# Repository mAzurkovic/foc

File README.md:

# FOC controller for a 7025 drone motor

Field-oriented control of a 7025 hobby motor (420 kV, 28 poles) with current,
speed and position loops, running at 20 kHz on an STM32, with space-vector
modulation, planned position moves and a measured cogging-torque table.

## Hardware

| Part | Used here |
|---|---|
| Controller | NUCLEO-F446RE |
| Driver | BOOSTXL-DRV8305EVM (3-PWM mode, low-side shunts) |
| Encoder | AS5048A over SPI, powered from 3.3 V |
| Supply | 12 V 10 A mains adapter (cannot absorb braking energy) |

Wiring, Nucleo Arduino-header names:

| Signal | Pin |
|---|---|
| DRV8305 PWMHA / PWMHB / PWMHC | D7 / D8 / D2 |
| DRV8305 SCS, ENGATE, FAULT | D9, D6, D5 |
| DRV8305 ISENA / ISENB / ISENC, VSENPVDD | A0 / A1 / A2, A3 |
| AS5048A CSn | D10 |
| Shared SPI: SCK, MISO, MOSI | D13, D12, D11 |
| AS5048A 3.3V and 5V pins | both to Nucleo 3V3 |

Leave the DRV8305 board's own 3.3V pin unconnected.

## Layout

- `nucleo_foc/` — the controller. This is the sketch to use.
- `legacy/` — earlier steps, kept for reference: Arduino Uno bring-up and
  control sketches (`drv8305_*`, `encoder_read`, ...), tests for a
  DRV8323RS board that turned out to have a faulty phase, and the Nucleo
  bring-up sketches. `legacy/nucleo_check` (wiring check, no PWM) and
  `legacy/nucleo_pwm_test` (resistance and inductance measurement) are still
  useful when changing hardware.
- `docs/` — driver and evaluation-board datasheets.

## Running it

Arduino IDE with the "STM32 MCU based boards" package and STM32CubeProgrammer.
Tools: Board **Nucleo-64**, Board part number **Nucleo F446RE**, Upload method
**STM32CubeProgrammer (SWD)**. Serial Monitor at 115200 baud, line ending
**Newline**.

Clamp the motor, nothing on the shaft, then type `g`.

| Command | Effect |
|---|---|
| `p<deg>` | planned move to an angle (accelerate, cruise, brake), then hold; prints the time taken |
| `v<rpm>` | speed control (up to 1000) |
| `q<amps>`, `d<amps>` | torque current, and d-axis current (no torque) |
| `s` | hold the present position |
| `x` | outputs off, motor coasts |
| `a` | re-measure encoder offset and direction |
| `C` | scan cogging torque and store the table in flash |
| `t` | measure acceleration per amp and retune the outer loops |
| `c0` / `c1` | cogging and friction feed-forward off / on |
| `W`, `R`, `B`, `O`, `D`, `P`, `K`, `I` | loop bandwidths, spacing and gains |
| `m<rows>` | status rows per second, `m0` for none |

Settings typed at run time are lost on reset; the defaults live at the top of
the sketch. The cogging table is the exception: it is kept in flash.

## Measured values (the sketch's defaults)

| Quantity | Value |
|---|---|
| Phase resistance, inductance | 0.030 Ω, 5.5 µH |
| Pole pairs | 14 |
| Back-EMF | about 1.75 mV per rpm (phase amplitude) |
| Acceleration per amp, bare shaft | 2900 rpm/s per A |
| Loop bandwidths | current 500 Hz, speed 50 Hz, position 5 Hz |
| Limits | 12 A target, 18 A trip, 1000 rpm, 3 V phase voltage |
| Planned moves | up to 900 rpm, accelerate 20,000 rpm/s, brake 8,000 rpm/s |

## When something changes

- **Motor wires moved, or encoder magnet remounted:** run `a`, update
  `encoderOffset` and `direction` in the sketch, then run `C`.
- **Anything attached to the shaft:** run `t`; the stored tuning is for a bare
  rotor.
- **Different supply:** braking energy is burned in the motor windings because
  this adapter shuts down when current flows back into it. The thresholds
  (`BUS_DUMP_START_VOLTS` and neighbours) assume a 12 V bus.

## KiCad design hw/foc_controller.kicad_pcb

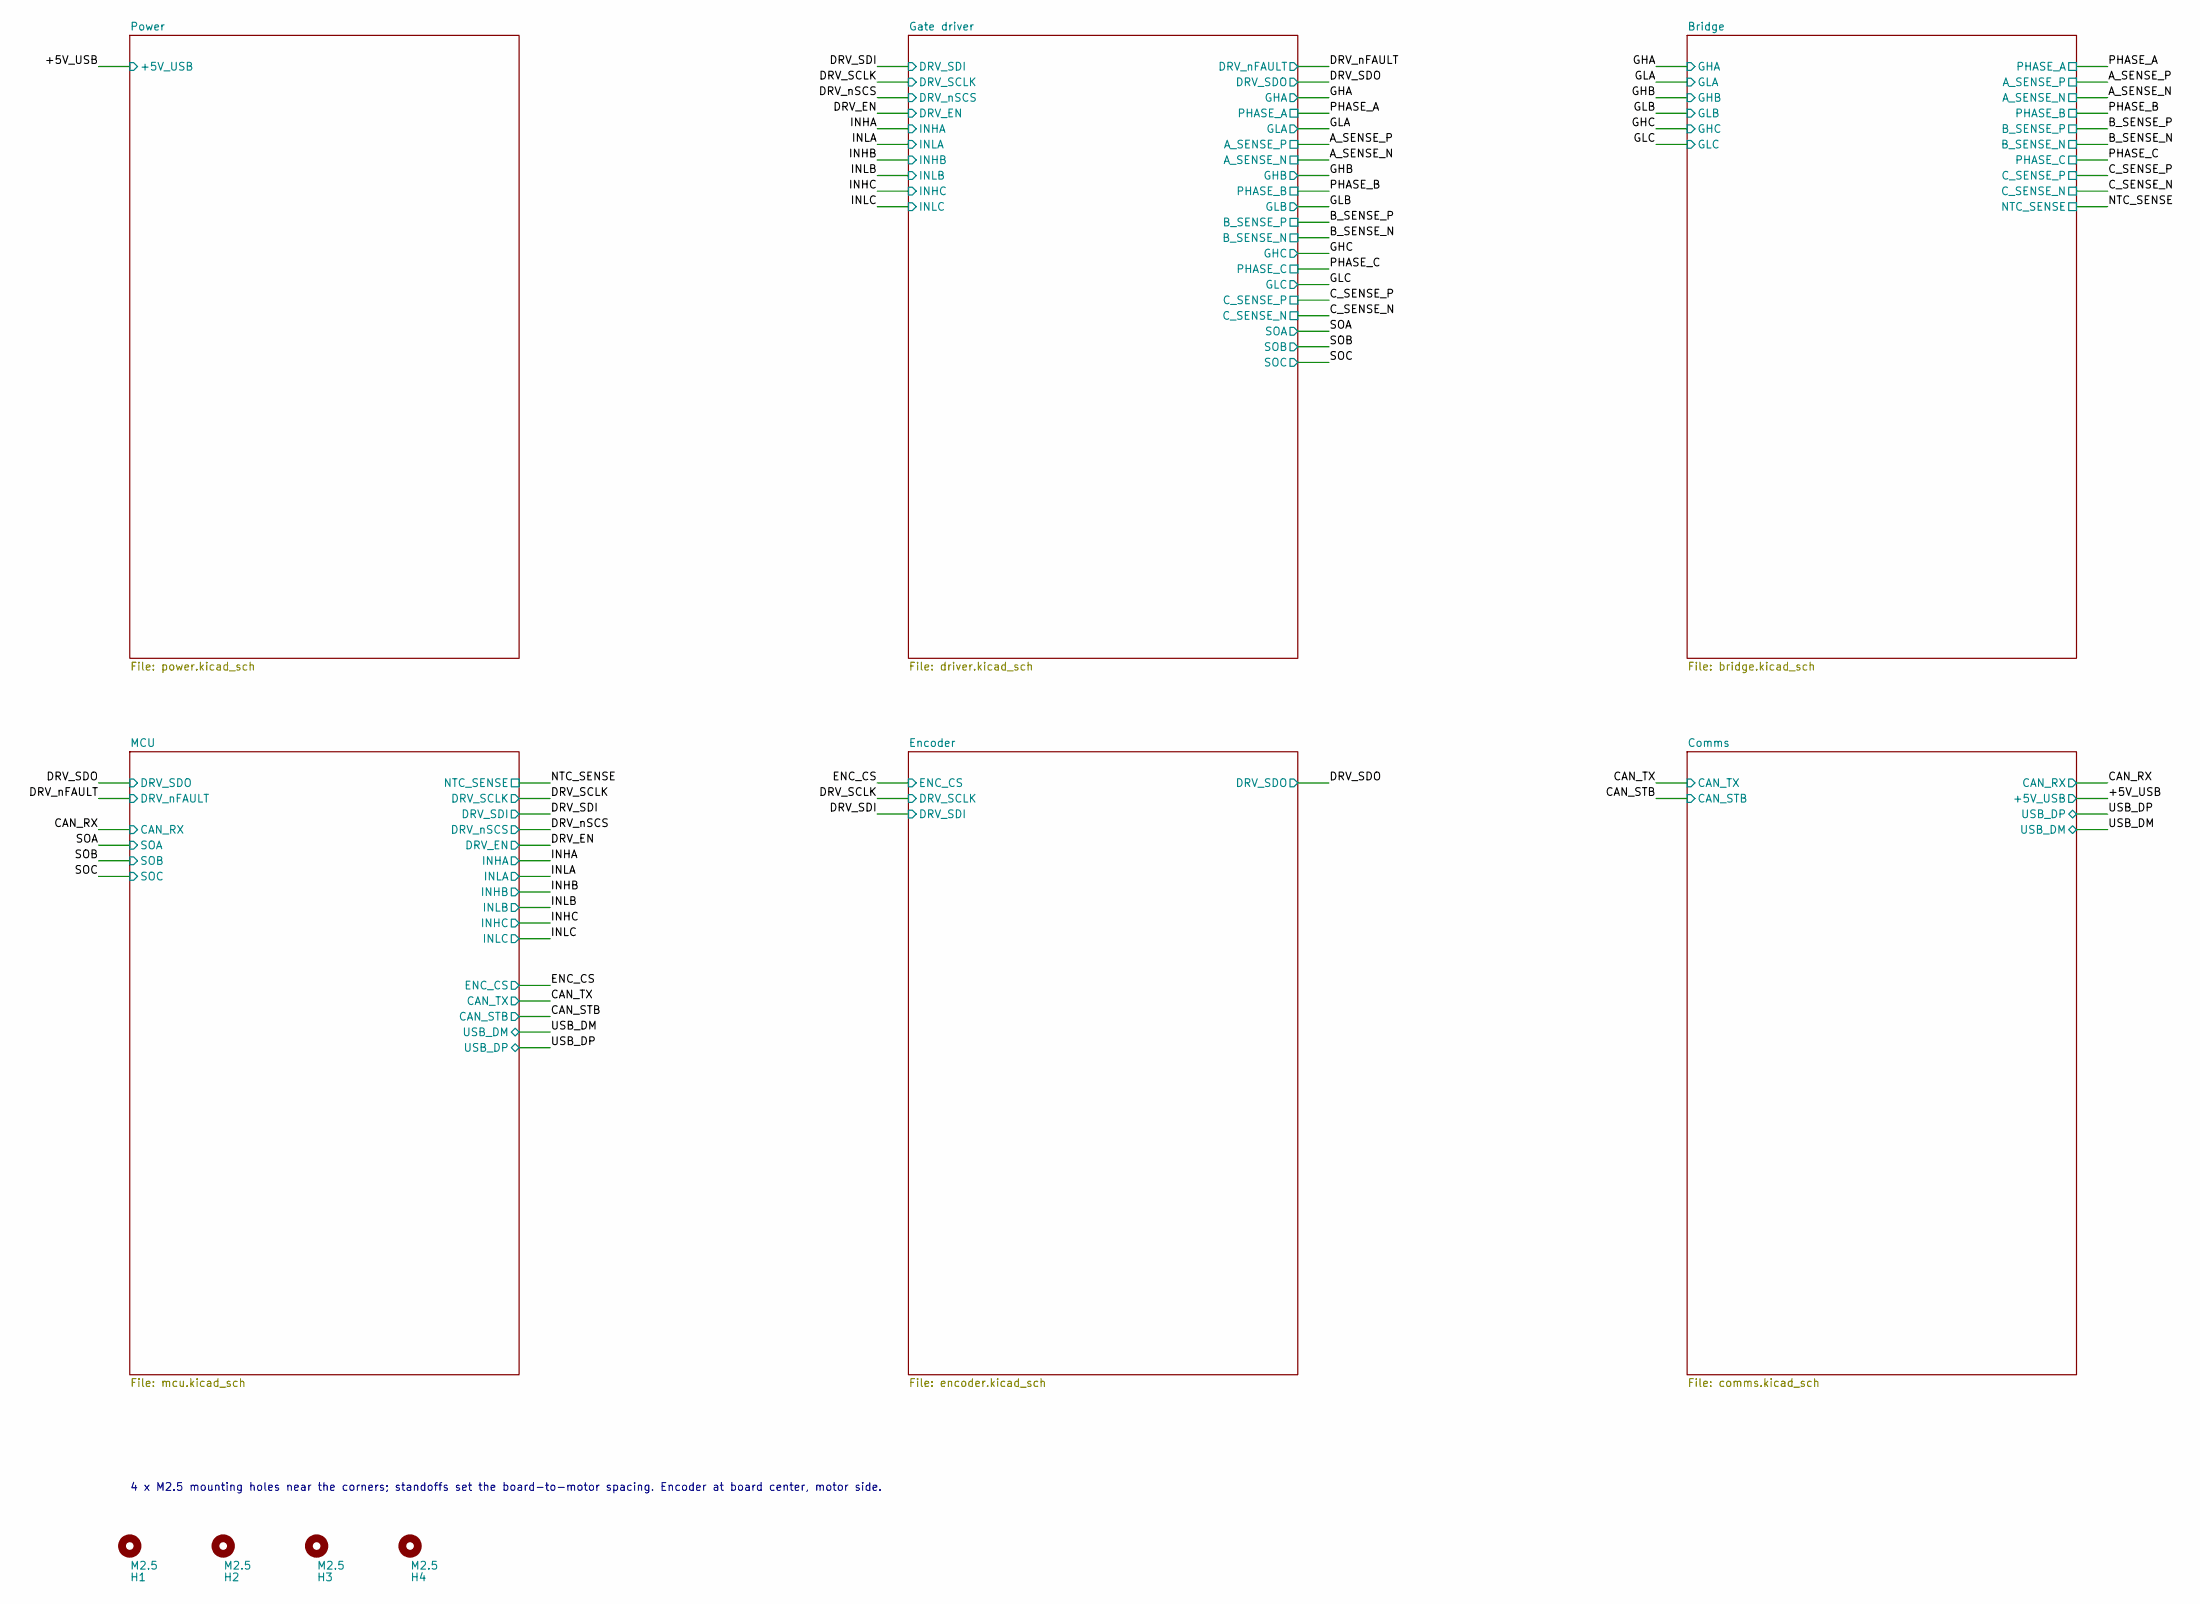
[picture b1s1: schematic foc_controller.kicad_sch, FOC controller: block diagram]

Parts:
H1, H2, H3, H4: M2.5; MountingHole_2.7mm_M2.5

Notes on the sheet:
4 x M2.5 mounting holes near the corners; standoffs set the board-to-motor spacing. Encoder at board center, motor side.

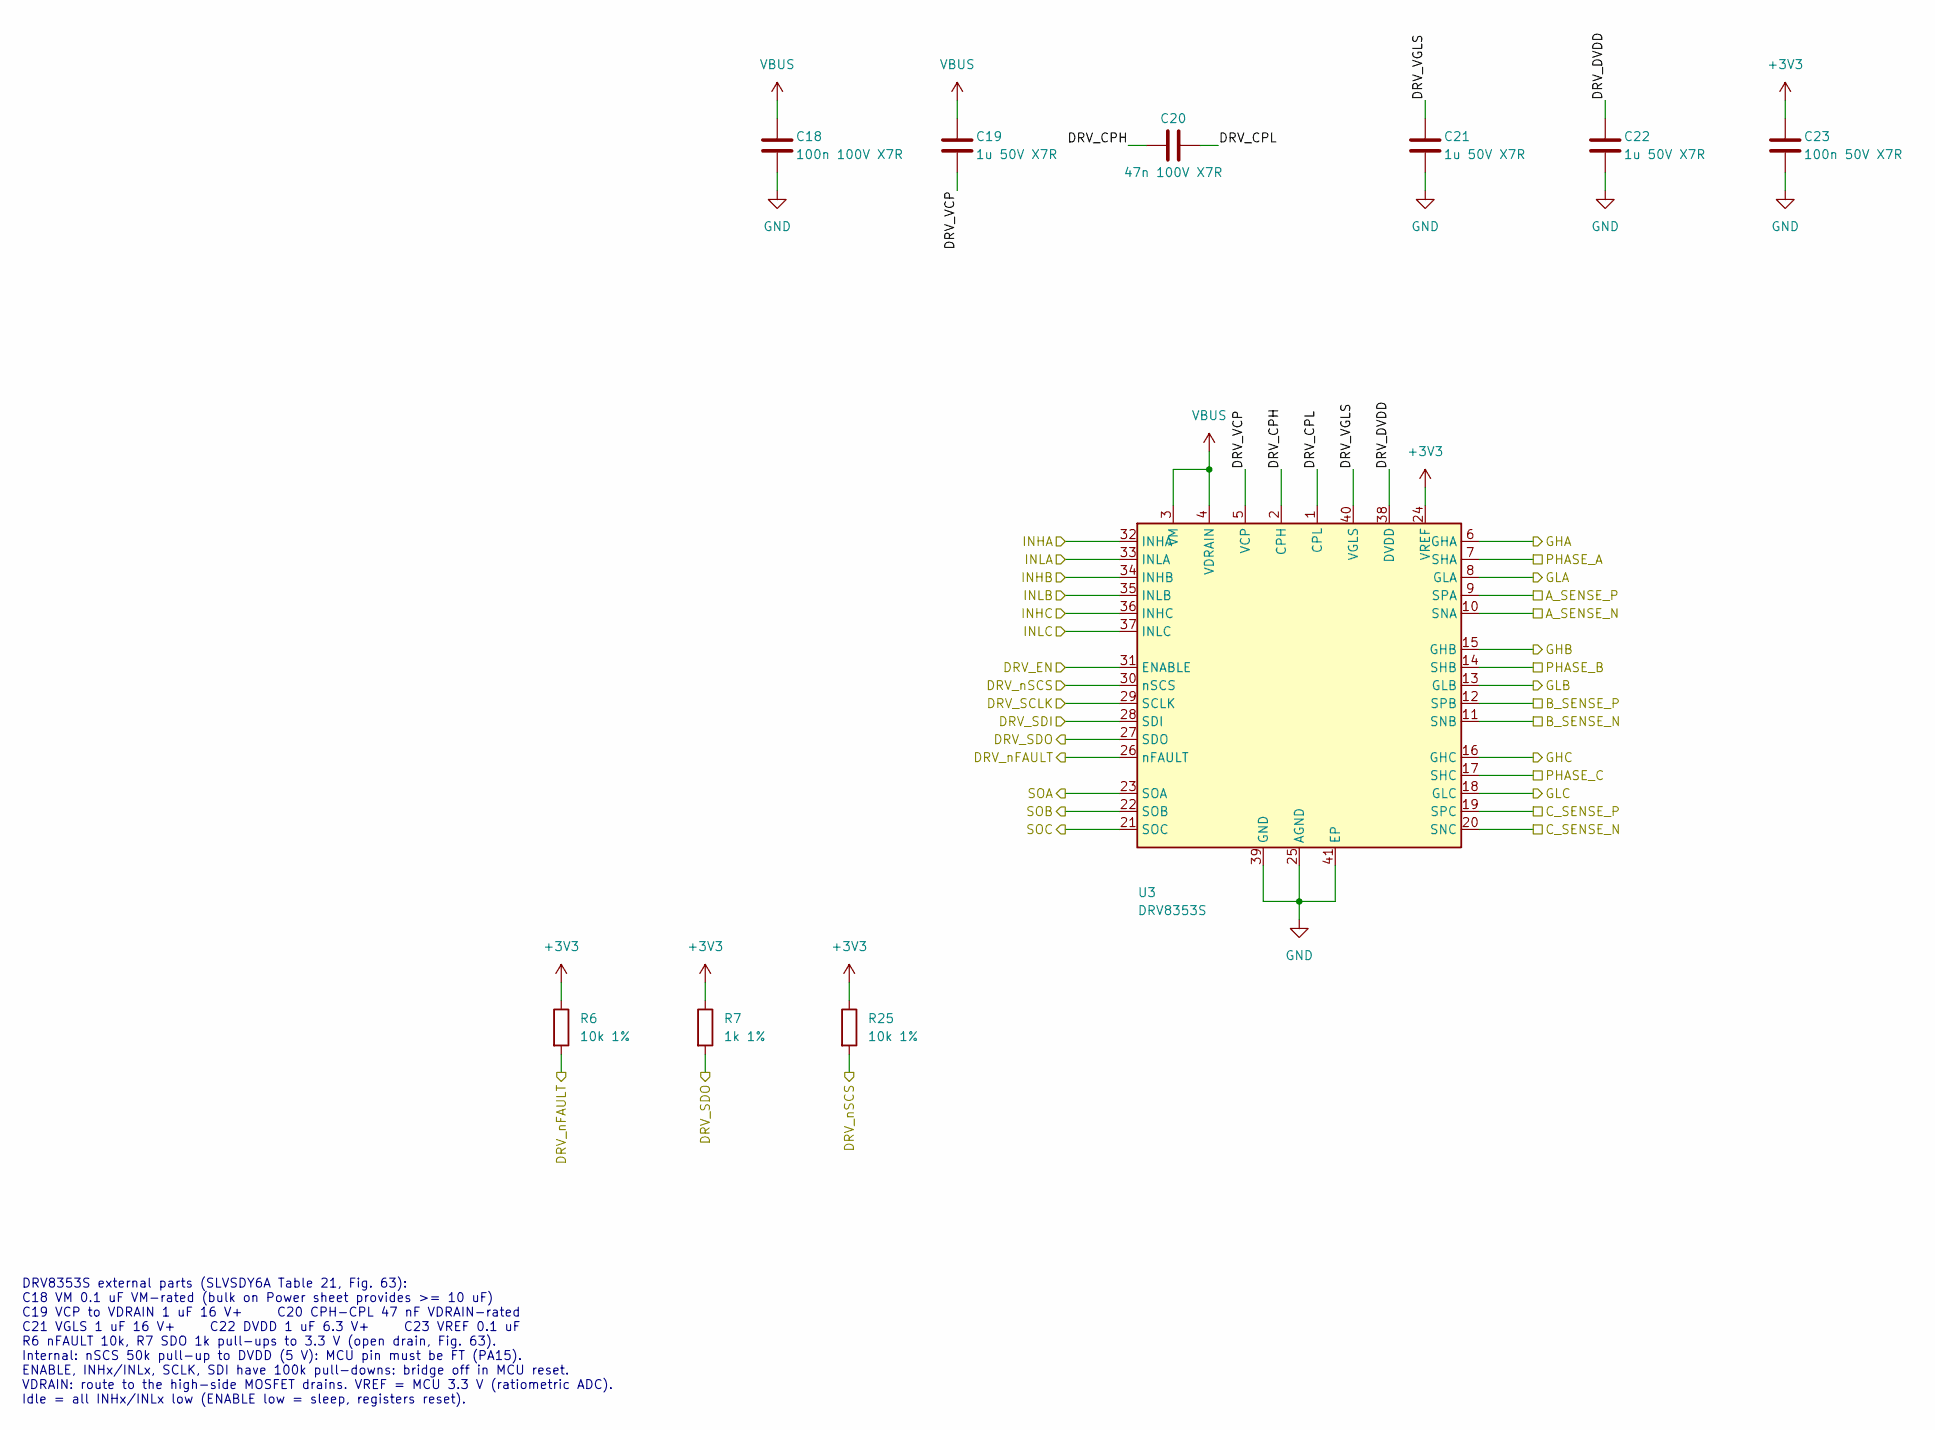
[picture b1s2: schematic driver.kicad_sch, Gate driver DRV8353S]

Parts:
C18: 100n 100V X7R; C_0603_1608Metric; MPN CC0603KRX7R0BB104; LCSC C113803
C19, C21, C22: 1u 50V X7R; C_0805_2012Metric; MPN CL21B105KBFNNNE; LCSC C28323
C20: 47n 100V X7R; C_0805_2012Metric; MPN CL21B473KCFNNNE; LCSC C17074
C23: 100n 50V X7R; C_0402_1005Metric; MPN CL05B104KB54PNC; LCSC C307331
R6, R25: 10k 1%; R_0402_1005Metric; MPN 0402WGF1002TCE; LCSC C25744
R7: 1k 1%; R_0402_1005Metric; MPN 0402WGF1001TCE; LCSC C11702
U3: DRV8353S; WQFN-40_L6.0-W6.0-P0.50-TL-EP4.2; MPN DRV8353SRTAT; LCSC C2150480

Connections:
+3V3: C23.1, R6.1, R7.1, R25.1, U3.24 (VREF); also elsewhere on the board
/A_SENSE_N: U3.10 (SNA); also elsewhere on the board
/A_SENSE_P: U3.9 (SPA); also elsewhere on the board
/B_SENSE_N: U3.11 (SNB); also elsewhere on the board
/B_SENSE_P: U3.12 (SPB); also elsewhere on the board
/C_SENSE_N: U3.20 (SNC); also elsewhere on the board
/C_SENSE_P: U3.19 (SPC); also elsewhere on the board
/DRV_EN: U3.31 (ENABLE); also elsewhere on the board
/DRV_SCLK: U3.29 (SCLK); also elsewhere on the board
/DRV_SDI: U3.28 (SDI); also elsewhere on the board
/DRV_SDO: R7.2, U3.27 (SDO); also elsewhere on the board
/DRV_nFAULT: R6.2, U3.26 (nFAULT); also elsewhere on the board
/DRV_nSCS: R25.2, U3.30 (nSCS); also elsewhere on the board
/GHA: U3.6 (GHA); also elsewhere on the board
/GHB: U3.15 (GHB); also elsewhere on the board
/GHC: U3.16 (GHC); also elsewhere on the board
/GLA: U3.8 (GLA); also elsewhere on the board
/GLB: U3.13 (GLB); also elsewhere on the board
/GLC: U3.18 (GLC); also elsewhere on the board
/Gate driver/DRV_CPH: C20.1, U3.2 (CPH)
/Gate driver/DRV_CPL: C20.2, U3.1 (CPL)
/Gate driver/DRV_DVDD: C22.1, U3.38 (DVDD)
/Gate driver/DRV_VCP: C19.1, U3.5 (VCP)
/Gate driver/DRV_VGLS: C21.1, U3.40 (VGLS)
/INHA: U3.32 (INHA); also elsewhere on the board
/INHB: U3.34 (INHB); also elsewhere on the board
/INHC: U3.36 (INHC); also elsewhere on the board
/INLA: U3.33 (INLA); also elsewhere on the board
/INLB: U3.35 (INLB); also elsewhere on the board
/INLC: U3.37 (INLC); also elsewhere on the board
/PHASE_A: U3.7 (SHA); also elsewhere on the board
/PHASE_B: U3.14 (SHB); also elsewhere on the board
/PHASE_C: U3.17 (SHC); also elsewhere on the board
/SOA: U3.23 (SOA); also elsewhere on the board
/SOB: U3.22 (SOB); also elsewhere on the board
/SOC: U3.21 (SOC); also elsewhere on the board
GND: C18.2, C21.2, C22.2, C23.2, U3.25 (AGND), U3.39 (GND), U3.41 (EP); also elsewhere on the board
VBUS: C18.1, C19.2, U3.3 (VM), U3.4 (VDRAIN); also elsewhere on the board

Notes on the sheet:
DRV8353S external parts (SLVSDY6A Table 21, Fig. 63): C18 VM 0.1 uF VM-rated (bulk on Power sheet provides >= 10 uF) C19 VCP to VDRAIN 1 uF 16 V+ C20 CPH-CPL 47 nF VDRAIN-rated C21 VGLS 1 uF 16 V+ C22 DVDD 1 uF 6.3 V+ C23 VREF 0.1 uF R6 nFAULT 10k, R7 SDO 1k pull-ups to 3.3 V (open drain, Fig. 63).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

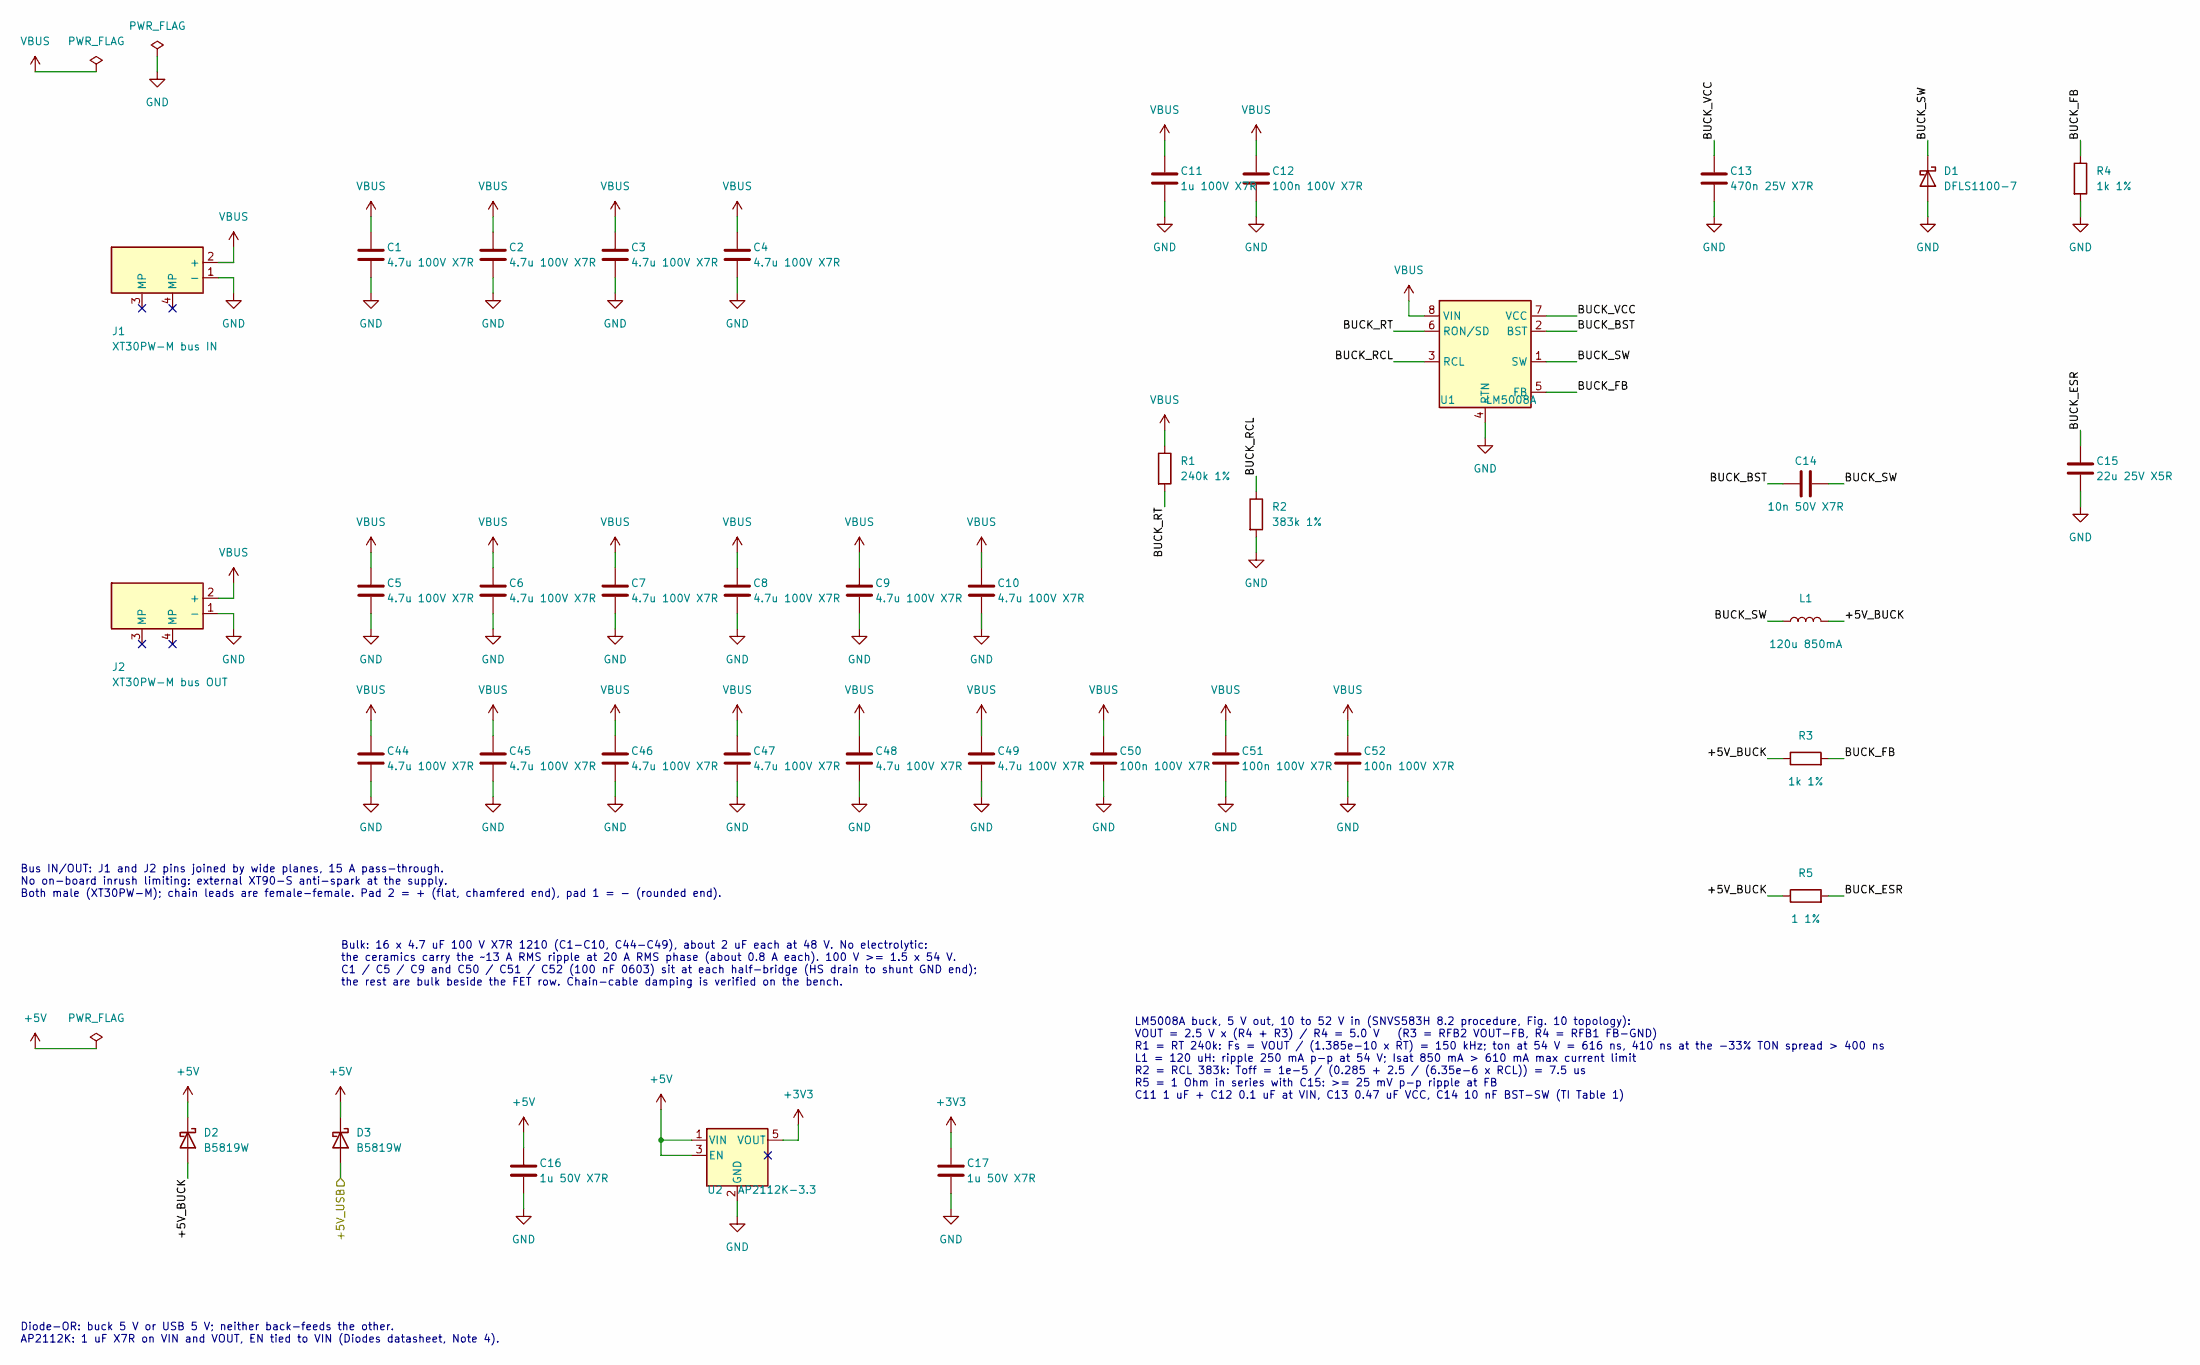
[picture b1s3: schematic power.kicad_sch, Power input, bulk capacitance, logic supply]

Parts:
C1, C2, C3, C4, C5, C6, C7, C8, C9, C10, C44, C45, C46, C47, C48, C49: 4.7u 100V X7R; C_1210_3225Metric; MPN FS32X475K101EGG; LCSC C381466
C11: 1u 100V X7R; C_1206_3216Metric; MPN CC1206KKX7R0BB105; LCSC C70463
C12, C50, C51, C52: 100n 100V X7R; C_0603_1608Metric; MPN CC0603KRX7R0BB104; LCSC C113803
C13: 470n 25V X7R; C_0603_1608Metric; MPN CL10B474KA8NNNC; LCSC C1623
C14: 10n 50V X7R; C_0603_1608Metric; MPN 0603B103K500NT; LCSC C57112
C15: 22u 25V X5R; C_1206_3216Metric; MPN CL31A226KAHNNNE; LCSC C12891
C16, C17: 1u 50V X7R; C_0805_2012Metric; MPN CL21B105KBFNNNE; LCSC C28323
D1: DFLS1100-7; D_PowerDI-123; MPN DFLS1100-7; LCSC C107674
D2, D3: B5819W; D_SOD-123; MPN B5819W SL; LCSC C8598
J1: XT30PW-M bus IN; CONN-TH_XT30PW-M-1; MPN XT30PW-M30.G.Y; LCSC C431092
J2: XT30PW-M bus OUT; CONN-TH_XT30PW-M-1; MPN XT30PW-M30.G.Y; LCSC C431092
L1: 120u 850mA; IND-SMD_L6.0-W6.0; MPN SWPA6045S121MT; LCSC C96952
R1: 240k 1%; R_0603_1608Metric; MPN RC0603FR-07240KL; LCSC C137765
R2: 383k 1%; R_0603_1608Metric; MPN 0603WAF3833T5E; LCSC C25816
R3, R4: 1k 1%; R_0402_1005Metric; MPN 0402WGF1001TCE; LCSC C11702
R5: 1 1%; R_0603_1608Metric; MPN 0603WAF100KT5E; LCSC C22936
U1: LM5008A; MSOP-8_3x3mm_P0.65mm; MPN LM5008AMMX/NOPB; LCSC C2071250
U2: AP2112K-3.3; SOT-23-5; MPN AP2112K-3.3TRG1; LCSC C51118

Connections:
+3V3: C17.1, U2.5 (VOUT); also elsewhere on the board
+5V: C16.1, D2.1 (K), D3.1 (K), U2.1 (VIN), U2.3 (EN)
/+5V_USB: D3.2 (A); also elsewhere on the board
/Power/+5V_BUCK: D2.2 (A), L1.2, R3.1, R5.1
/Power/BUCK_BST: C14.1, U1.2 (BST)
/Power/BUCK_ESR: C15.1, R5.2
/Power/BUCK_FB: R3.2, R4.1, U1.5 (FB)
/Power/BUCK_RCL: R2.1, U1.3 (RCL)
/Power/BUCK_RT: R1.2, U1.6 (RON/SD)
/Power/BUCK_SW: C14.2, D1.1 (K), L1.1, U1.1 (SW)
/Power/BUCK_VCC: C13.1, U1.7 (VCC)
GND: C1.2, C2.2, C3.2, C4.2, C5.2, C6.2, C7.2, C8.2, C9.2, C10.2, C11.2, C12.2, C13.2, C15.2, C16.2, C17.2, C44.2, C45.2, C46.2, C47.2, C48.2, C49.2, C50.2, C51.2, C52.2, D1.2 (A), J1.1 (-), J2.1 (-), R2.2, R4.2, U1.4 (RTN), U2.2 (GND); also elsewhere on the board
VBUS: C1.1, C2.1, C3.1, C4.1, C5.1, C6.1, C7.1, C8.1, C9.1, C10.1, C11.1, C12.1, C44.1, C45.1, C46.1, C47.1, C48.1, C49.1, C50.1, C51.1, C52.1, J1.2 (+), J2.2 (+), R1.1, U1.8 (VIN); also elsewhere on the board

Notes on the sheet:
Diode-OR: buck 5 V or USB 5 V; neither back-feeds the other. AP2112K: 1 uF X7R on VIN and VOUT, EN tied to VIN (Diodes datasheet, Note 4).
Bus IN/OUT: J1 and J2 pins joined by wide planes, 15 A pass-through. No on-board inrush limiting: external XT90-S anti-spark at the supply. Both male (XT30PW-M); chain leads are female-female. Pad 2 = + (flat, chamfered end), pad 1 = - (rounded end).
LM5008A buck, 5 V out, 10 to 52 V in (SNVS583H 8.2 procedure, Fig. 10 topology): VOUT = 2.5 V x (R4 + R3) / R4 = 5.0 V (R3 = RFB2 VOUT-FB, R4 = RFB1 FB-GND) R1 = RT 240k: Fs = VOUT / (1.385e-10 x RT) = 150 kHz; ton at 54 V = 616 ns, 410 ns at the -33% TON spread > 400 ns L1 = 120 uH: ripple 250 mA 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
Bulk: 16 x 4.7 uF 100 V X7R 1210 (C1-C10, C44-C49), about 2 uF each at 48 V. No electrolytic: the ceramics carry the ~13 A RMS ripple at 20 A RMS phase (about 0.8 A each). 100 V >= 1.5 x 54 V. C1 / C5 / C9 and C50 / C51 / C52 (100 nF 0603) sit at each half-bridge (HS drain to shunt GND end); the re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

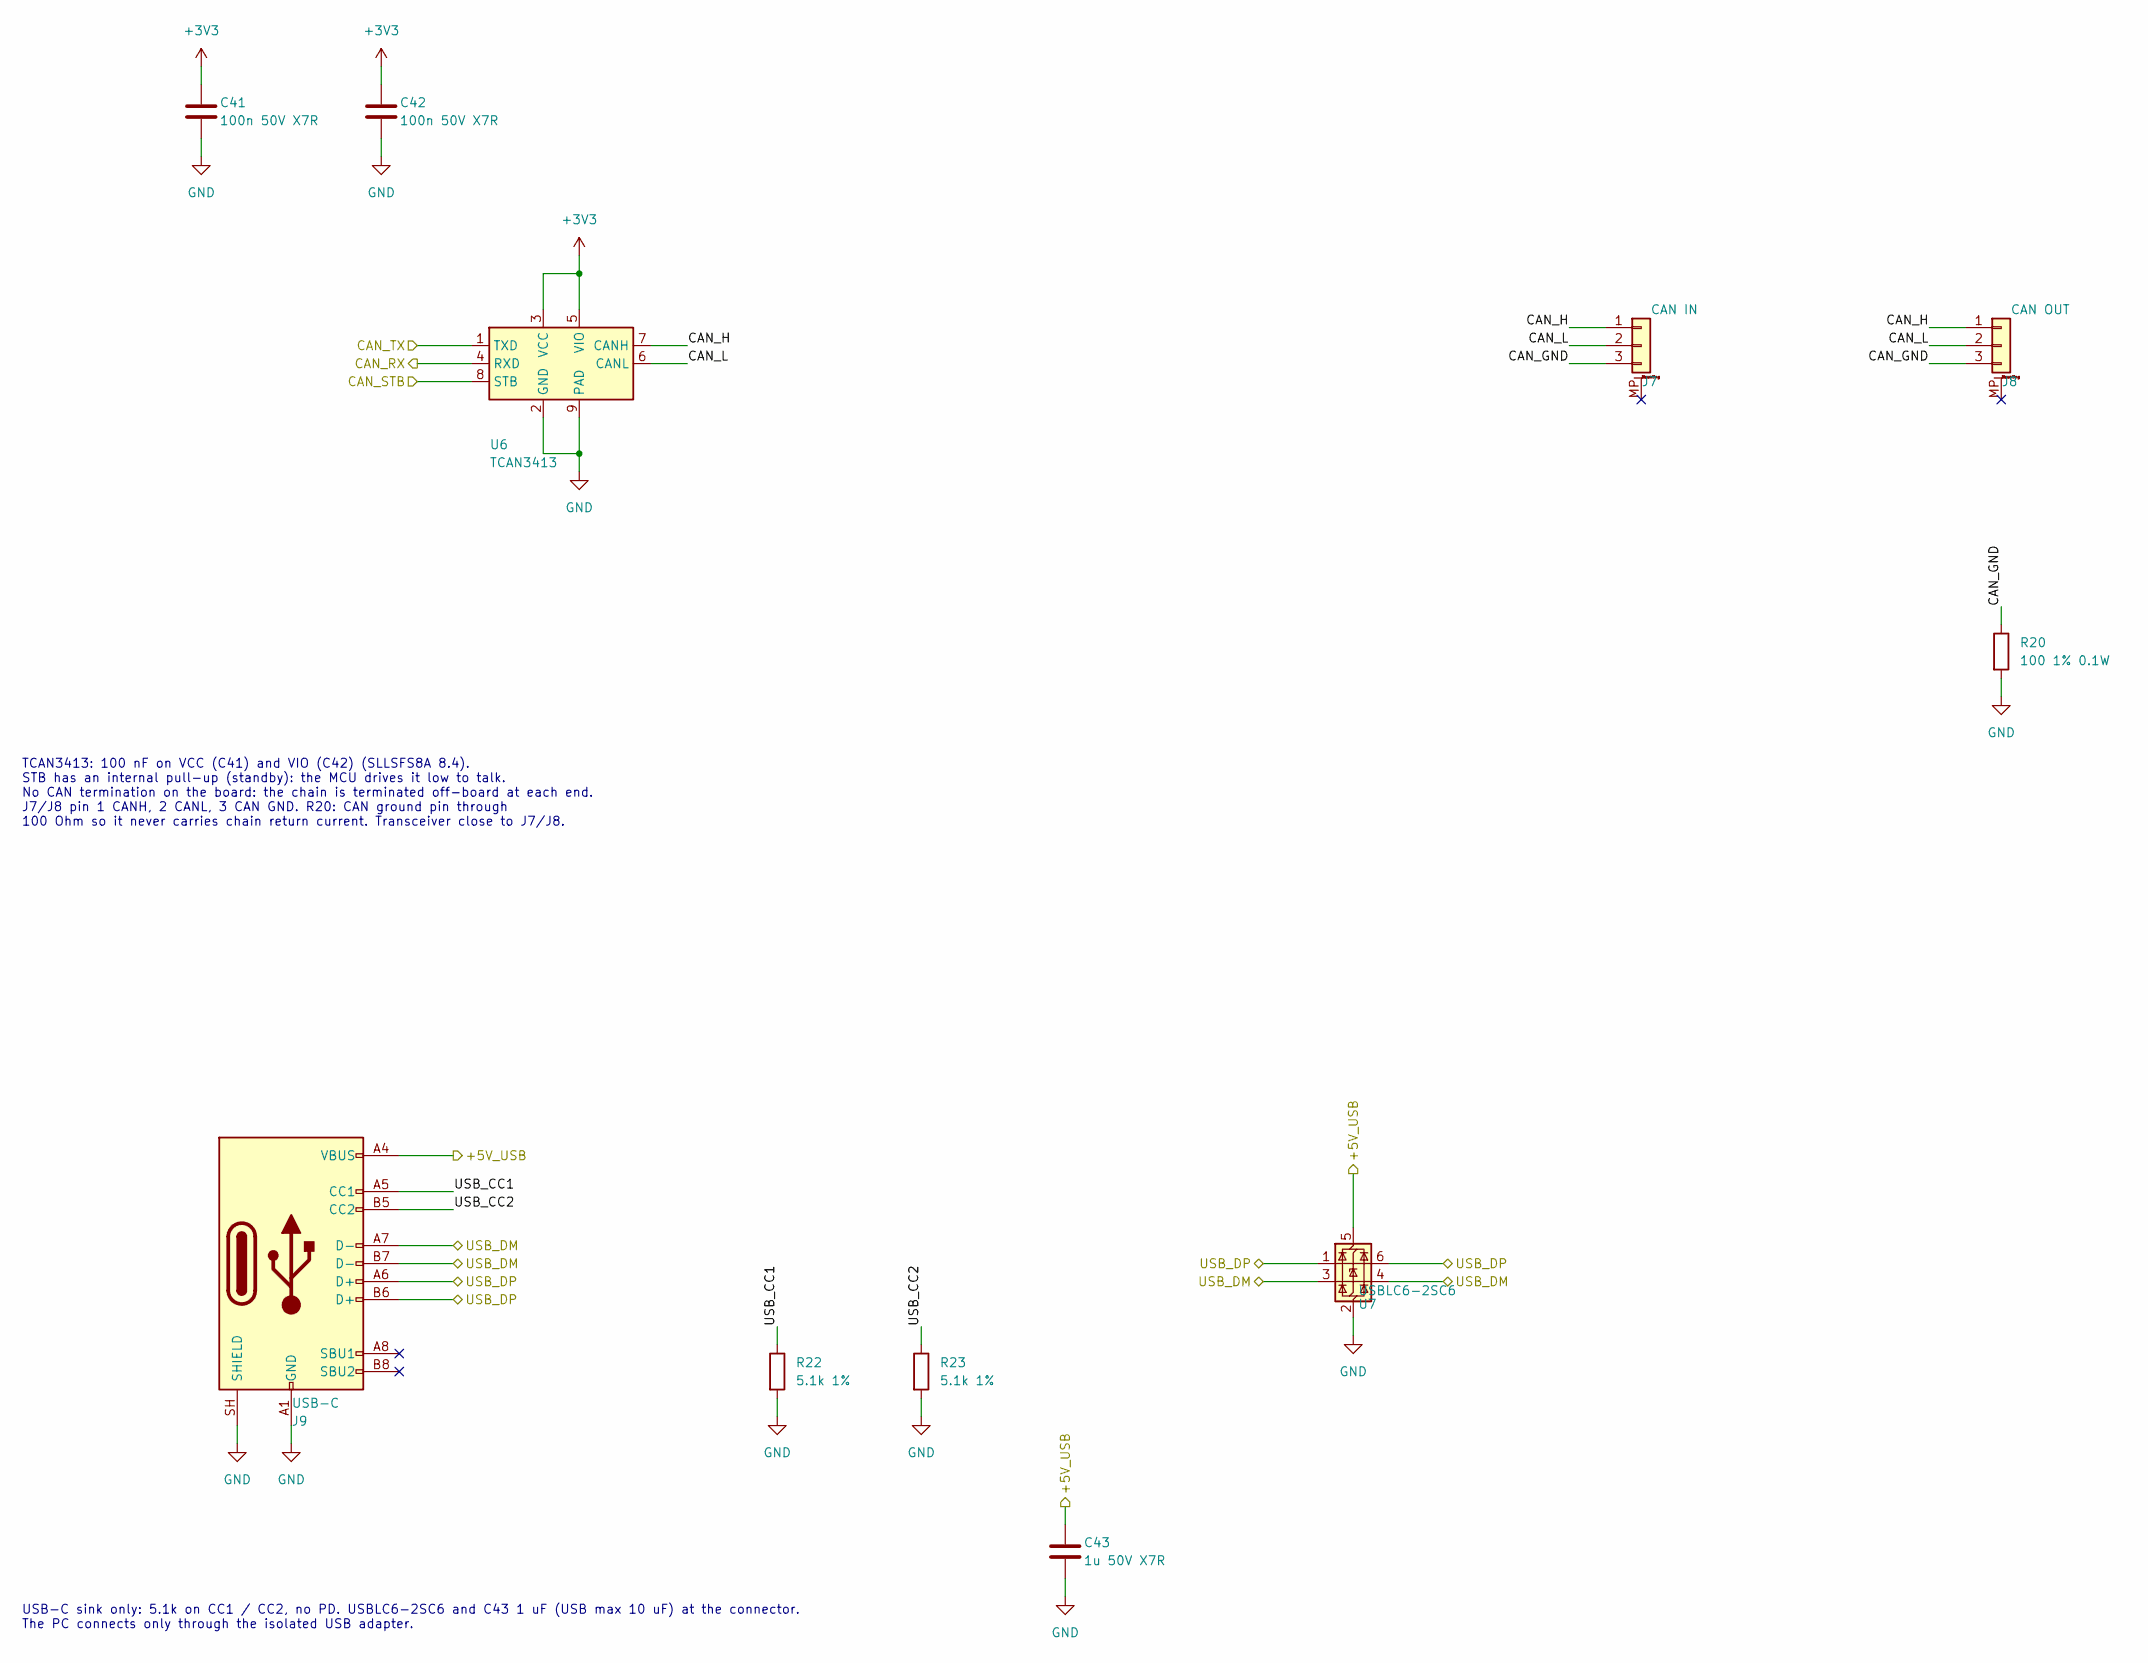
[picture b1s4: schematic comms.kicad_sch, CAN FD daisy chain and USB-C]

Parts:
C41, C42: 100n 50V X7R; C_0402_1005Metric; MPN CL05B104KB54PNC; LCSC C307331
C43: 1u 50V X7R; C_0805_2012Metric; MPN CL21B105KBFNNNE; LCSC C28323
J7: CAN IN; JST_GH_SM03B-GHS-TB_1x03-1MP_P1.25mm_Horizontal; MPN SM03B-GHS-TB(LF)(SN); LCSC C514175
J8: CAN OUT; JST_GH_SM03B-GHS-TB_1x03-1MP_P1.25mm_Horizontal; MPN SM03B-GHS-TB(LF)(SN); LCSC C514175
J9: USB-C; USB_C_Receptacle_HRO_TYPE-C-31-M-12; MPN TYPE-C-31-M-12; LCSC C165948
R20: 100 1% 0.1W; R_0603_1608Metric; MPN 0603WAF1000T5E; LCSC C22775
R22, R23: 5.1k 1%; R_0402_1005Metric; MPN 0402WGF5101TCE; LCSC C25905
U6: TCAN3413; SON-8_L3.0-W3.0-P0.65-LS2.9-BL-EP; MPN TCAN3413DRBR; LCSC C22445415
U7: USBLC6-2SC6; SOT-23-6; MPN USBLC6-2SC6; LCSC C2687116

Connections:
+3V3: C41.1, C42.1, U6.3 (VCC), U6.5 (VIO); also elsewhere on the board
/+5V_USB: C43.1, J9.A4 (VBUS), J9.A9 (VBUS), J9.B4 (VBUS), J9.B9 (VBUS), U7.5 (VBUS); also elsewhere on the board
/CAN_RX: U6.4 (RXD); also elsewhere on the board
/CAN_STB: U6.8 (STB); also elsewhere on the board
/CAN_TX: U6.1 (TXD); also elsewhere on the board
/Comms/CAN_GND: J7.3, J8.3, R20.1
/Comms/CAN_H: J7.1, J8.1, U6.7 (CANH)
/Comms/CAN_L: J7.2, J8.2, U6.6 (CANL)
/Comms/USB_CC1: J9.A5 (CC1), R22.1
/Comms/USB_CC2: J9.B5 (CC2), R23.1
/USB_DM: J9.A7 (D-), J9.B7 (D-), U7.3 (I/O2), U7.4 (I/O2); also elsewhere on the board
/USB_DP: J9.A6 (D+), J9.B6 (D+), U7.1 (I/O1), U7.6 (I/O1); also elsewhere on the board
GND: C41.2, C42.2, C43.2, J9.A1 (GND), J9.A12 (GND), J9.B1 (GND), J9.B12 (GND), J9.SH (SHIELD), R20.2, R22.2, R23.2, U6.2 (GND), U6.9 (PAD), U7.2 (GND); also elsewhere on the board

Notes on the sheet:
TCAN3413: 100 nF on VCC (C41) and VIO (C42) (SLLSFS8A 8.4). STB has an internal pull-up (standby): the MCU drives it low to talk. No CAN termination on the board: the chain is terminated off-board at each end. J7/J8 pin 1 CANH, 2 CANL, 3 CAN GND. R20: CAN ground pin through 100 Ohm so it never carr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
USB-C sink only: 5.1k on CC1 / CC2, no PD. USBLC6-2SC6 and C43 1 uF (USB max 10 uF) at the connector. The PC connects only through the isolated USB adapter.
